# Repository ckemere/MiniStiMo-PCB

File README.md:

# Rodent DBS module PCBs

KiCAD design for a small scale constant current stimulator which can be controlled via BLE from a smartphone

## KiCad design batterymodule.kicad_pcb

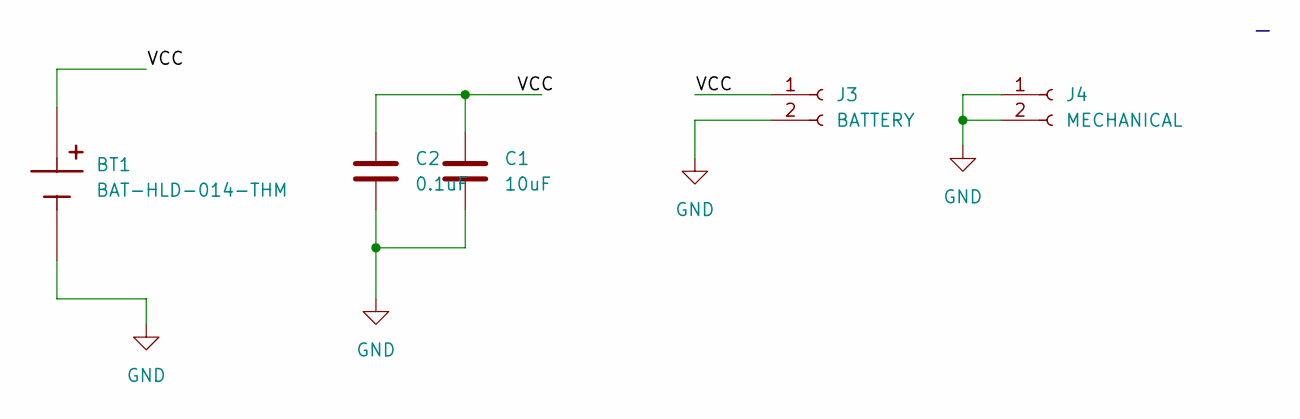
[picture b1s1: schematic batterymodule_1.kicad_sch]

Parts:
BT1: BAT-HLD-014-THM; BAT_BAT-HLD-014-THM
C1: 10uF; C_0603_1608Metric; Manufacturer_Part_Number 04026D106MAT2A
C2: 0.1uF; C_0402_1005Metric; Manufacturer_Part_Number 04023D104KAT2A
J3: BATTERY; PinHeader_1x02_P2.54mm_Vertical
J4: MECHANICAL; PinHeader_1x02_P2.54mm_Vertical

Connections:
/batterymodule_1/VCC: BT1.P_1, C1.1, C2.1, J3.1
GND: BT1.N, C1.2, C2.2, J3.2, J4.1, J4.2

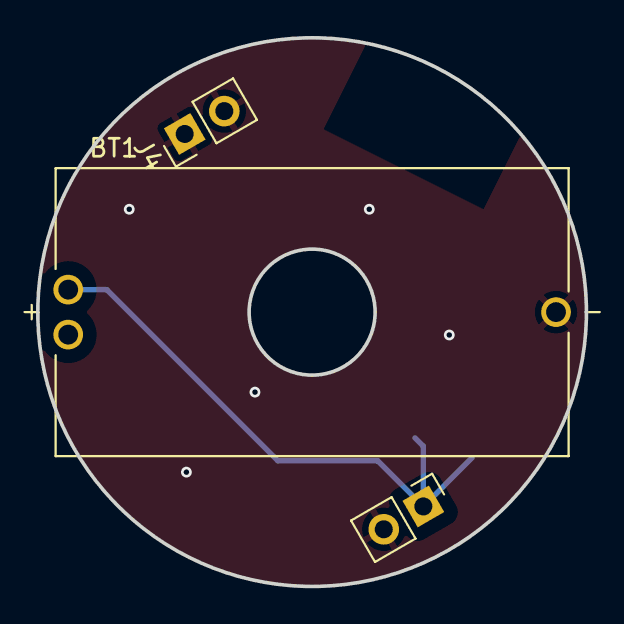
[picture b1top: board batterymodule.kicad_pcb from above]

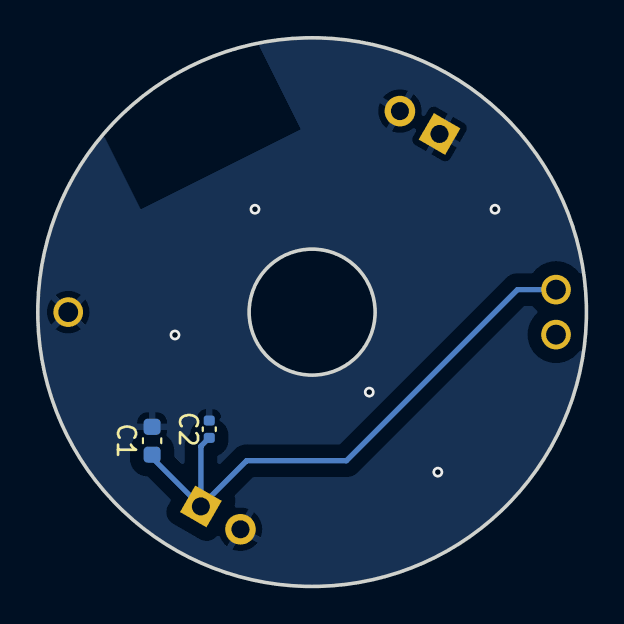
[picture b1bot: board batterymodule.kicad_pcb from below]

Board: 2 copper layers, 30.5 x 30.5 mm, 5 parts (2 on the bottom side), 2 nets.

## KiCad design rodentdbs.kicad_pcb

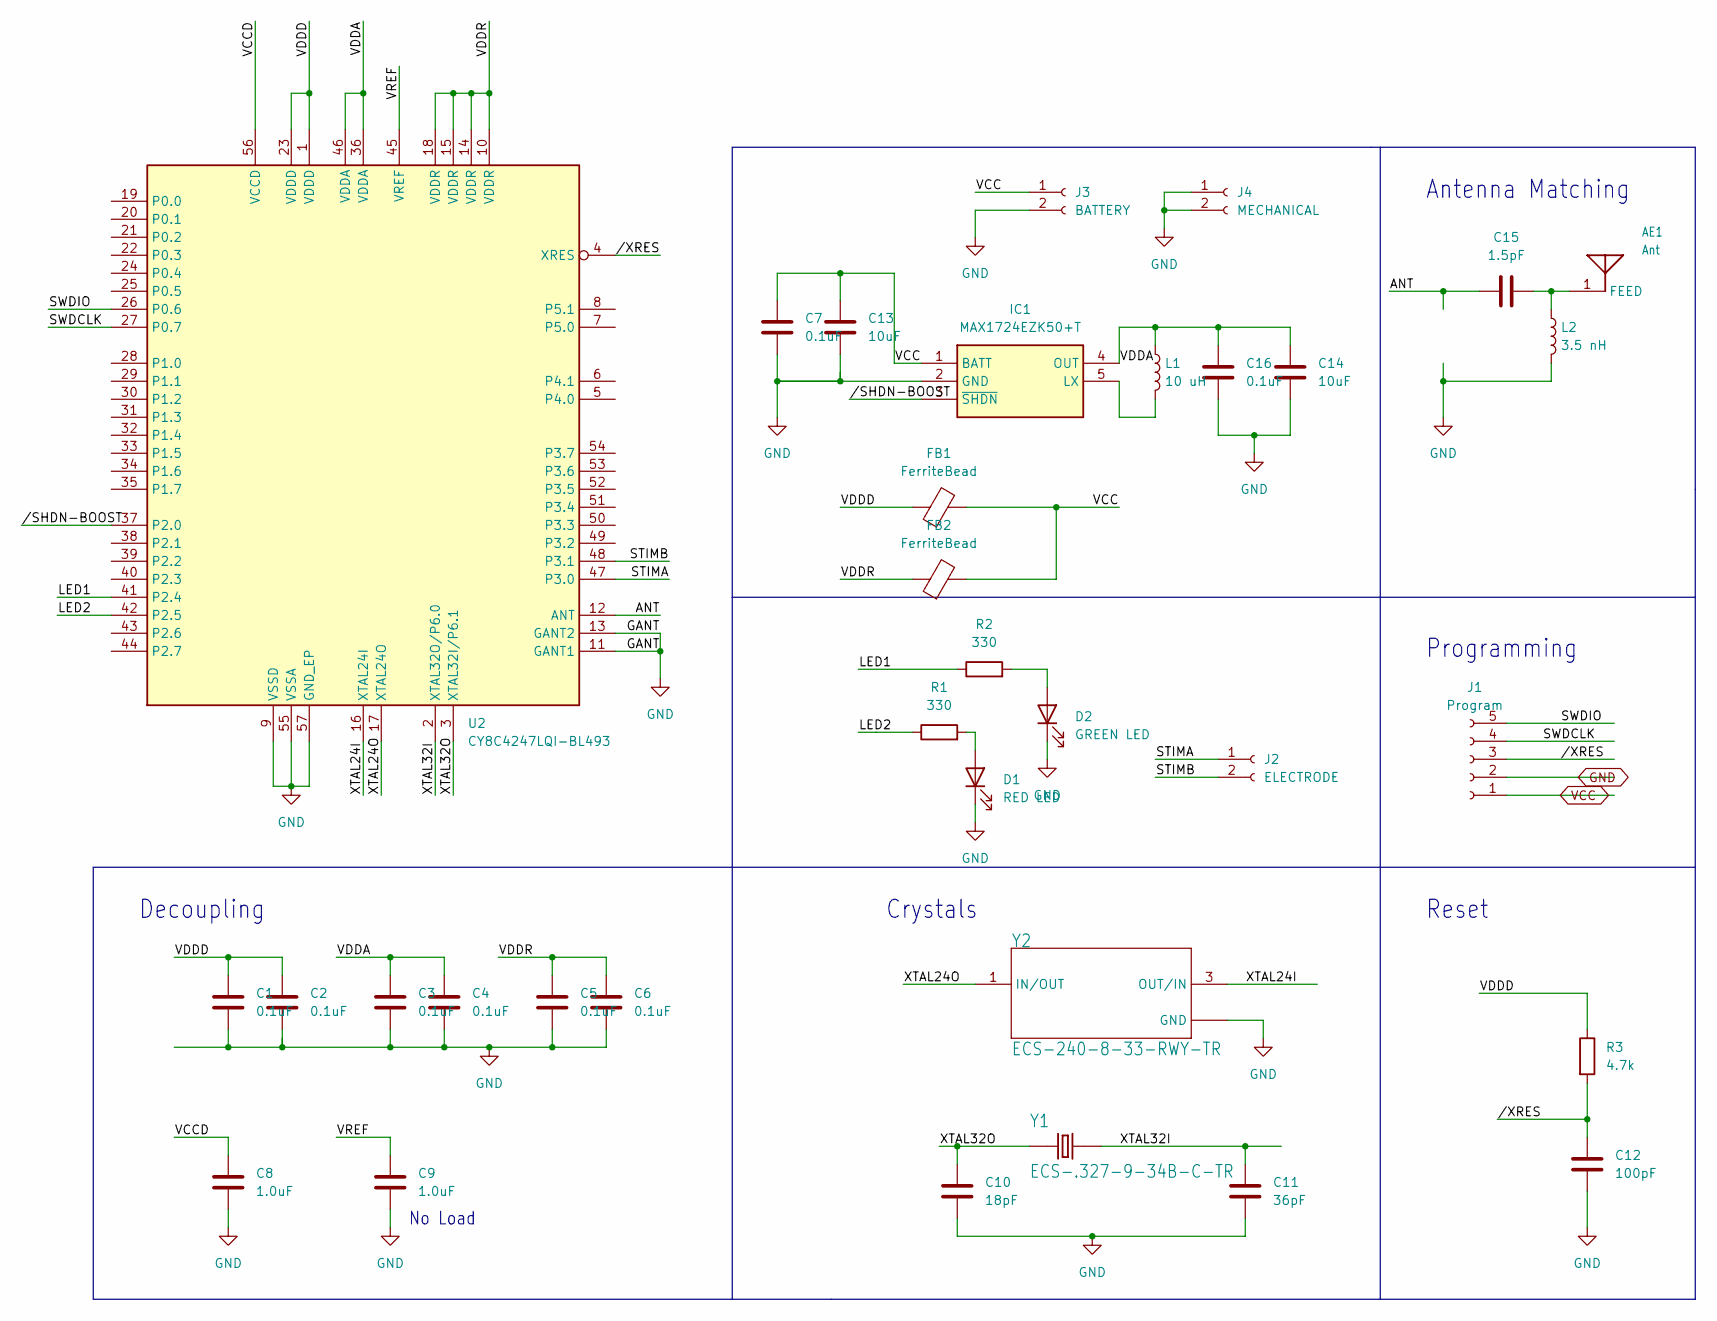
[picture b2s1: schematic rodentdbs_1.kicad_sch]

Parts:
AE1: Ant; XCVR_2450AT42B100E; Manufacturer_Part_Number 2450AT42B0100001E
C1, C2, C3, C4, C5, C6, C7, C16: 0.1uF; C_0402_1005Metric; Manufacturer_Part_Number 04023D104KAT2A
C8, C9: 1.0uF; C_0402_1005Metric; Manufacturer_Part_Number 0402X105K160CT
C10: 18pF; C_0402_1005Metric; Manufacturer_Part_Number 04025A180JAT2A
C11: 36pF; C_0402_1005Metric; Manufacturer_Part_Number 04025A360JAT2A
C12: 100pF; C_0402_1005Metric; Manufacturer_Part_Number 04025C101KAT2A
C13: 10uF; C_0603_1608Metric; Manufacturer_Part_Number 04026D106MAT2A
C14: 10uF; C_0603_1608Metric; Manufacturer_Part_Number 06033D106MAT2A
C15: 1.5pF; C_0402_1005Metric; Manufacturer_Part_Number GJM1555C1HR15BB01D
D1: RED LED; LED_0402_1005Metric; Manufacturer_Part_Number 150040RS73240
D2: GREEN LED; LED_0402_1005Metric; Manufacturer_Part_Number 150040VS73240
FB1, FB2: FerriteBead; L_0402_1005Metric; Manufacturer_Part_Number BLM15AX221SN1D
IC1: MAX1724EZK50+T; SOT95P275X110-5N; Mouser Part Number 700-MAX1724EZK50T
J1: Program; PinHeader_1x05_P1.27mm_Vertical
J2: ELECTRODE; PinHeader_1x02_P1.27mm_Vertical
J3: BATTERY; PinHeader_1x02_P2.54mm_Vertical
J4: MECHANICAL; PinHeader_1x02_P2.54mm_Vertical
L1: 10 uH; L_1210_3225Metric; Manufacturer_Part_Number 1277AS-H-100M=P2
L2: 3.5 nH; L_0402_1005Metric; Manufacturer_Part_Number LQG15HS3N9S02D
R1, R2: 330; R_0402_1005Metric; Manufacturer_Part_Number ERJ-2GEJ331X
R3: 4.7k; R_0402_1005Metric; Manufacturer_Part_Number ERA-2VEB4701X
U2: CY8C4247LQI-BL493; QFN-56-1EP_7x7mm_P0.4mm_EP5.6x5.6mm; Manufacturer_Part_Number CY8C4247LQI-BL493
Y1: ECS-.327-9-34B-C-TR; XTAL_ECS-.327-9-34B-C-TR; Manufacturer_Part_Number ECS-.327-9-34B-C-TR
Y2: ECS-240-8-33-RWY-TR; XTAL_ECS-240-8-33-RWY-TR; Manufacturer_Part_Number ECS-240-8-33-RWY-TR

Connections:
/rodentdbs_1/ANT: C15.1, U2.12 (ANT)
/rodentdbs_1/LED1: R2.1, U2.41 (P2.4)
/rodentdbs_1/LED2: R1.1, U2.42 (P2.5)
/rodentdbs_1/STIMA: J2.1, U2.47 (P3.0)
/rodentdbs_1/STIMB: J2.2, U2.48 (P3.1)
/rodentdbs_1/SWDCLK: J1.4, U2.27 (P0.7)
/rodentdbs_1/SWDIO: J1.5, U2.26 (P0.6)
/rodentdbs_1/VCCD: C8.1, U2.56 (VCCD)
/rodentdbs_1/VDDA: C3.1, C4.1, C14.1, C16.1, IC1.4 (OUT), L1.1, U2.36 (VDDA), U2.46 (VDDA)
/rodentdbs_1/VDDD: C1.1, C2.1, FB1.1, R3.1, U2.1 (VDDD), U2.23 (VDDD)
/rodentdbs_1/VDDR: C5.1, C6.1, FB2.1, U2.10 (VDDR), U2.14 (VDDR), U2.15 (VDDR), U2.18 (VDDR)
/rodentdbs_1/VREF: C9.1, U2.45 (VREF)
/rodentdbs_1/XTAL24I: U2.16 (XTAL24I), Y2.3 (OUT/IN)
/rodentdbs_1/XTAL24O: U2.17 (XTAL24O), Y2.1 (IN/OUT)
/rodentdbs_1/XTAL32I: C11.1, U2.2 (XTAL32O/P6.0), Y1.2
/rodentdbs_1/XTAL32O: C10.1, U2.3 (XTAL32I/P6.1), Y1.1
/rodentdbs_1//SHDN-BOOST: IC1.3 (~SHDN), U2.37 (P2.0)
GND: C1.2, C2.2, C3.2, C4.2, C5.2, C6.2, C7.2, C8.2, C9.2, C10.2, C11.2, C12.2, C13.2, C14.2, C16.2, D1.1 (K), D2.1 (K), IC1.2 (GND), J1.2, J3.2, J4.1, J4.2, L2.2, U2.9 (VSSD), U2.11 (GANT1), U2.13 (GANT2), U2.55 (VSSA), U2.57 (GND_EP), Y2.2 (GND), Y2.4 (GND)
unnamed: AE1.1 (FEED), C15.2, L2.1
unnamed: D1.2 (A), R1.2
unnamed: D2.2 (A), R2.2
unnamed: IC1.5 (LX), L1.2
VCC: C7.1, C13.1, FB1.2, FB2.2, IC1.1 (BATT), J1.1, J3.1

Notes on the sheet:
Programming
No Load
Crystals
Antenna Matching
Decoupling
Reset

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
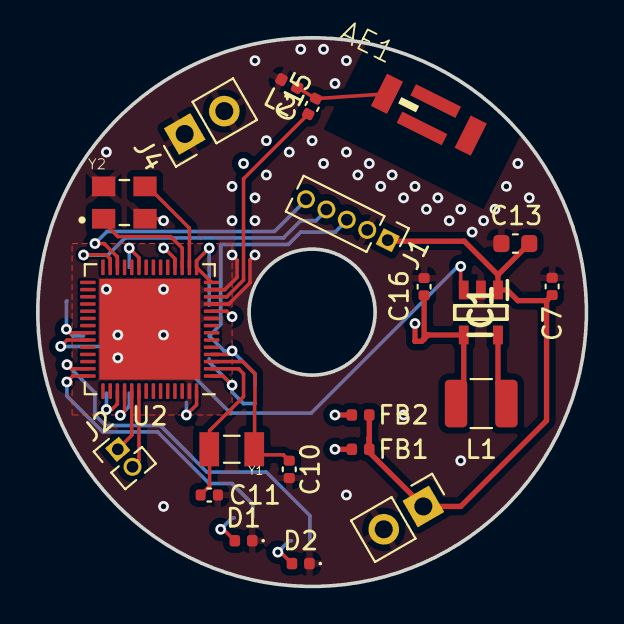
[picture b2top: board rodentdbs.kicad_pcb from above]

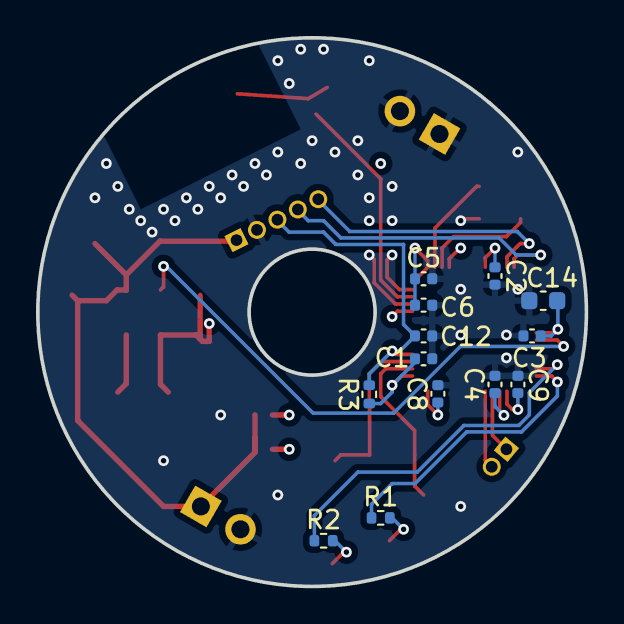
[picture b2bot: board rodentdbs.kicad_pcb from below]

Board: 4 copper layers, 30.5 x 30.5 mm, 34 parts (13 on the bottom side), 24 nets.

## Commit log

2023-10-25 Fixed capacitor layout error in Rev 1.0 design
2023-10-25 Added BatteryModule PCB
2023-10-25 Updated directory structure and restored Manufacturing files
2024-05-02 Added photo of built module
